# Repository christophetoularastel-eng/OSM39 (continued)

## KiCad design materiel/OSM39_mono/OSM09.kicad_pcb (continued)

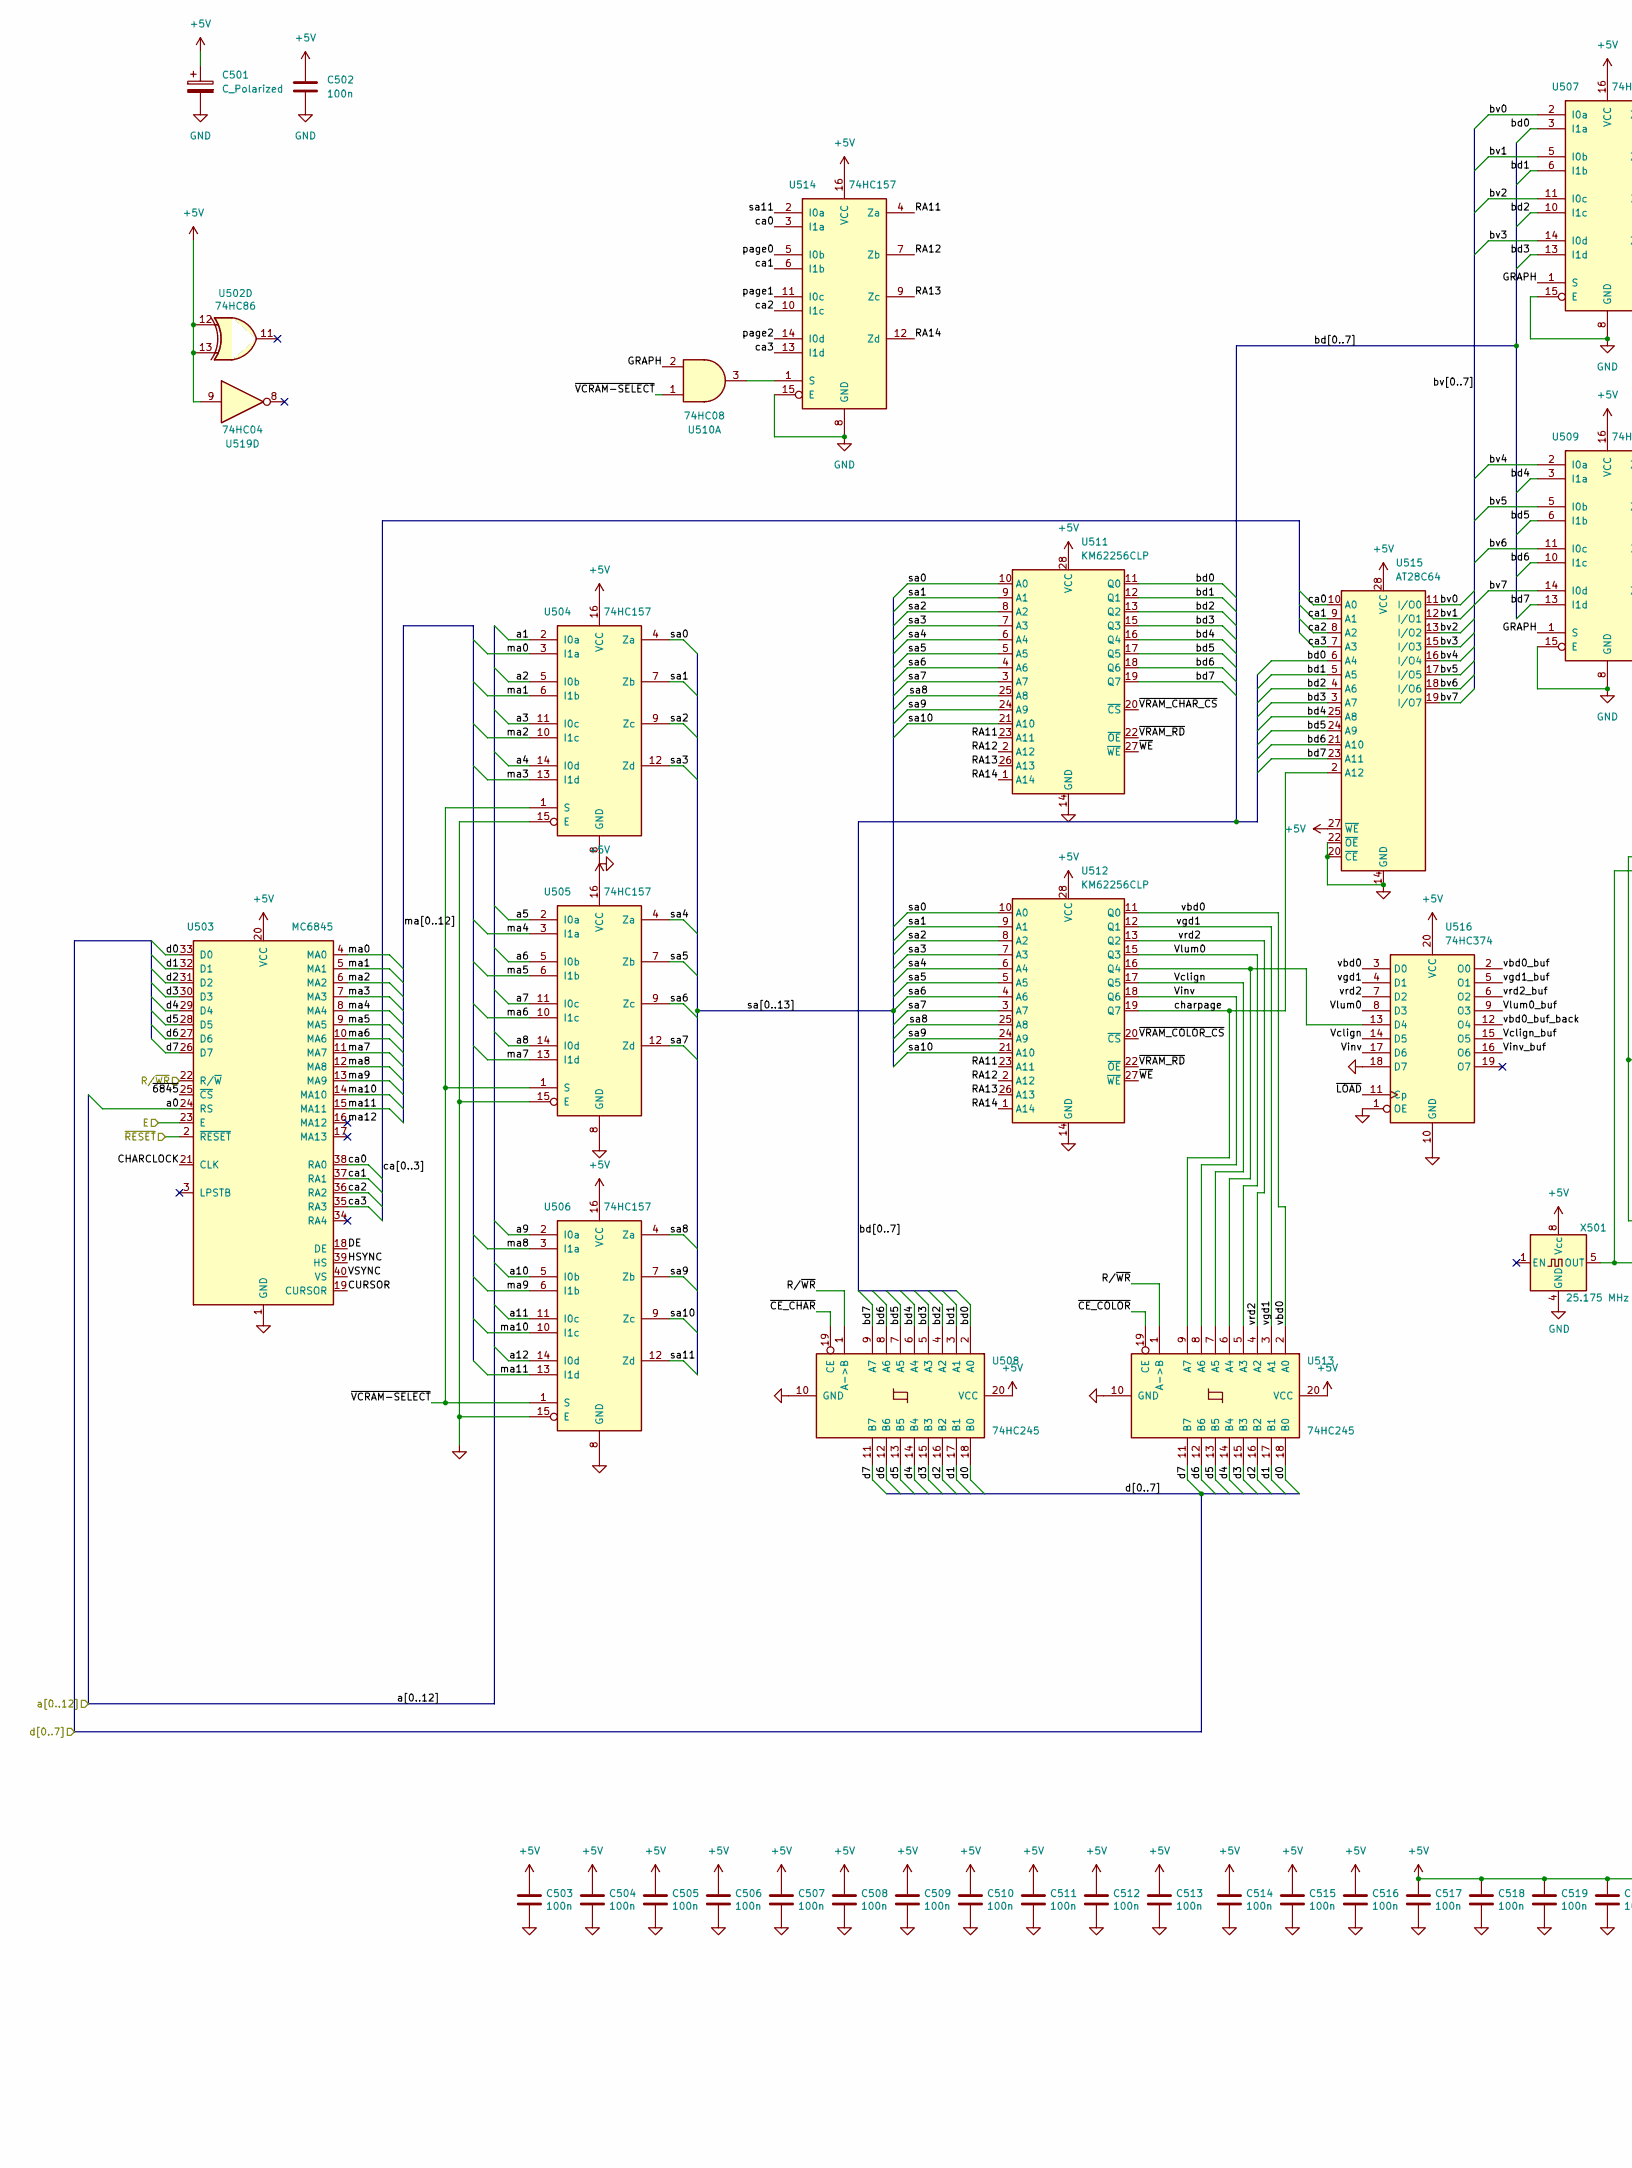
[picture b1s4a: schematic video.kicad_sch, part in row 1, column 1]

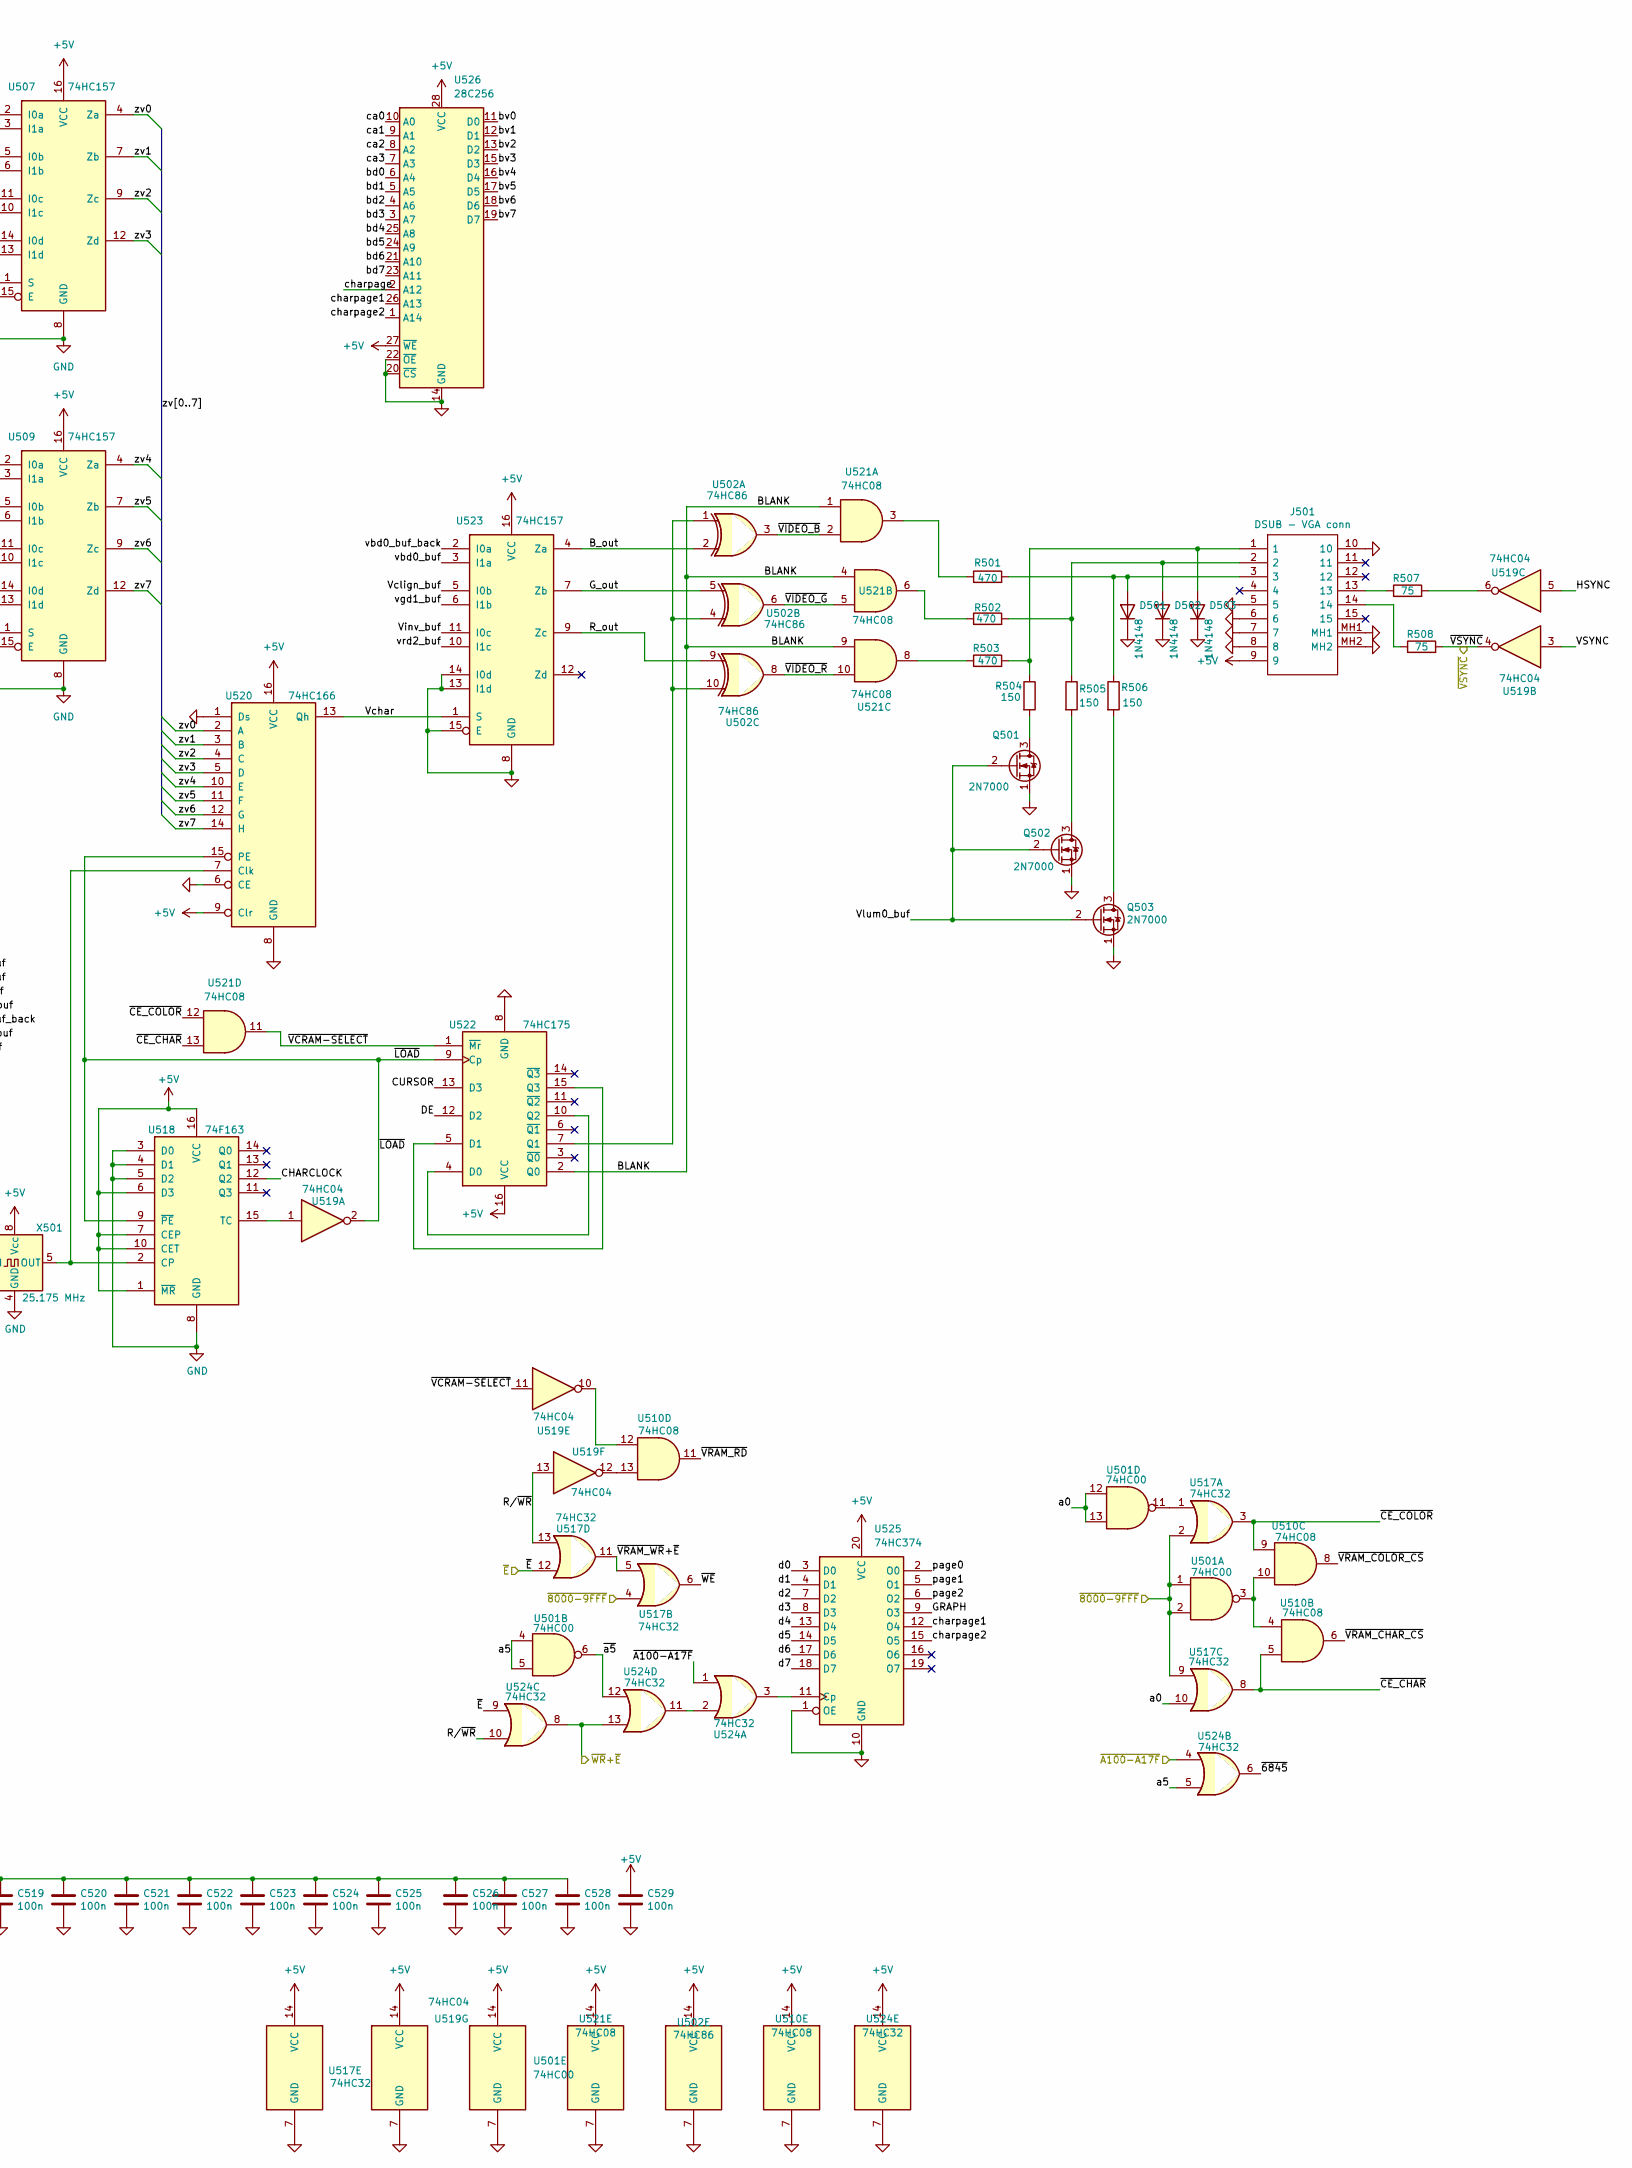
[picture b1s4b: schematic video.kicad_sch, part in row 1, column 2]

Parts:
C501: C_Polarized; CP_Radial_D4.0mm_P1.50mm
C502, C503, C504, C505, C506, C507, C508, C509, C510, C511, C512, C513, C514, C515, C516, C517, C518, C519, C520, C521, C522, C523, C524, C525, C526, C527, C528, C529: 100n; C_Disc_D5.0mm_W2.5mm_P2.50mm
D501, D502, D503: 1N4148; D_DO-35_SOD27_P7.62mm_Horizontal
J501: DSUB - VGA conn; D-Sub High Density Connectors; Mouser Part Number 571-2311586-4
Q501, Q502, Q503: 2N7000; TO-92_Inline
R501, R502, R503: 470; R_Axial_DIN0207_L6.3mm_D2.5mm_P10.16mm_Horizontal
R504, R505, R506: 150; R_Axial_DIN0207_L6.3mm_D2.5mm_P10.16mm_Horizontal
R507, R508: 75; R_Axial_DIN0207_L6.3mm_D2.5mm_P10.16mm_Horizontal
U501: 74HC00; DIP-14_W7.62mm_LongPads
U502: 74HC86; DIP-14_W7.62mm_LongPads
U503: MC6845; DIP-40_W15.24mm_LongPads
U504, U505, U506, U507, U509, U514, U523: 74HC157; DIP-16_W7.62mm_LongPads
U508, U513: 74HC245; DIP-20_W7.62mm_LongPads
U510, U521: 74HC08; DIP-14_W7.62mm_LongPads
U511, U512: KM62256CLP; DIP-28_W15.24mm_LongPads
U515: AT28C64; DIP-28_W15.24mm_LongPads
U516, U525: 74HC374; DIP-20_W7.62mm_LongPads
U517, U524: 74HC32; DIP-14_W7.62mm_LongPads
U518: 74F163; DIP-16_W7.62mm_LongPads
U519: 74HC04; DIP-14_W7.62mm_LongPads
U520: 74HC166; DIP-16_W7.62mm_LongPads
U522: 74HC175; DIP-16_W7.62mm_LongPads
U526: 28C256; DIP-28_W15.24mm_LongPads
X501: 25.175 MHz; Oscillator_DIP-8

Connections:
+5V: C501.1, C502.1, C503.1, C504.1, C505.1, C506.1, C507.1, C508.1, C509.1, C510.1, C511.1, C512.1, C513.1, C514.1, C515.1, C516.1, C517.1, C518.1, C519.1, C520.1, C521.1, C522.1, C523.1, C524.1, C525.1, C526.1, C527.1, C528.1, C529.1, J501.9, U501.14 (VCC), U502.12, U502.13, U502.14 (VCC), U503.20 (VCC), U504.16 (VCC), U505.16 (VCC), U506.16 (VCC), U507.16 (VCC), U508.20 (VCC), U509.16 (VCC), U510.14 (VCC), U511.28 (VCC), U512.28 (VCC), U513.20 (VCC), U514.16 (VCC), U515.27 (~WE), U515.28 (VCC), U516.20 (VCC), U517.14 (VCC), U518.1 (~MR), U518.6 (D3), U518.7 (CEP), U518.10 (CET), U518.16 (VCC), U519.9, U519.14 (VCC), U520.9 (Clr), U520.16 (VCC), U521.14 (VCC), U522.16 (VCC), U523.16 (VCC), U524.14 (VCC), U525.20 (VCC), U526.27 (~WE), U526.28 (VCC), X501.8 (Vcc); also elsewhere on the board
/8000-9FFF: U501.1, U501.2, U517.2, U517.4, U517.9; also elsewhere on the board
/A0: U501.12, U501.13, U503.24 (RS), U517.10; also elsewhere on the board
/A1: U504.2 (I0a); also elsewhere on the board
/A2: U504.5 (I0b); also elsewhere on the board
/A3: U504.11 (I0c); also elsewhere on the board
/A4: U504.14 (I0d); also elsewhere on the board
/A5: U501.4, U501.5, U505.2 (I0a), U524.5; also elsewhere on the board
/A6: U505.5 (I0b); also elsewhere on the board
/A7: U505.11 (I0c); also elsewhere on the board
/A8: U505.14 (I0d); also elsewhere on the board
/A9: U506.2 (I0a); also elsewhere on the board
/A10: U506.5 (I0b); also elsewhere on the board
/A11: U506.11 (I0c); also elsewhere on the board
/A12: U506.14 (I0d); also elsewhere on the board
/A100-A13F: U524.1, U524.4; also elsewhere on the board
/D0: U503.33 (D0), U508.18 (B0), U513.18 (B0), U525.3 (D0); also elsewhere on the board
/D1: U503.32 (D1), U508.17 (B1), U513.17 (B1), U525.4 (D1); also elsewhere on the board
/D2: U503.31 (D2), U508.16 (B2), U513.16 (B2), U525.7 (D2); also elsewhere on the board
/D3: U503.30 (D3), U508.15 (B3), U513.15 (B3), U525.8 (D3); also elsewhere on the board
/D4: U503.29 (D4), U508.14 (B4), U513.14 (B4), U525.13 (D4); also elsewhere on the board
/D5: U503.28 (D5), U508.13 (B5), U513.13 (B5), U525.14 (D5); also elsewhere on the board
/D6: U503.27 (D6), U508.12 (B6), U513.12 (B6), U525.17 (D6); also elsewhere on the board
/D7: U503.26 (D7), U508.11 (B7), U513.11 (B7), U525.18 (D7); also elsewhere on the board
/E: U503.23 (E); also elsewhere on the board
/R/~WR: U503.22 (R/~W), U508.1 (A->B), U513.1 (A->B), U517.13, U519.13, U524.10; also elsewhere on the board
/VSYNC: R508.2, U519.4; also elsewhere on the board
/video/BLANK: U521.1, U521.4, U521.9, U522.2 (Q0)
/video/B_out: U502.2, U523.4 (Za)
/video/CHARCLOCK: U503.21 (CLK), U518.12 (Q2)
/video/CURSOR: U503.19 (CURSOR), U522.13 (D3)
/video/DE: U503.18 (DE), U522.12 (D2)
/video/GRAPH: U507.1 (S), U509.1 (S), U510.2, U525.9 (O3)
/video/G_out: U502.5, U523.7 (Zb)
/video/HSYNC: U503.39 (HS), U519.5
/video/RA11: U511.23 (A11), U512.23 (A11), U514.4 (Za)
/video/RA12: U511.2 (A12), U512.2 (A12), U514.7 (Zb)
/video/RA13: U511.26 (A13), U512.26 (A13), U514.9 (Zc)
/video/RA14: U511.1 (A14), U512.1 (A14), U514.12 (Zd)
/video/R_out: U502.9, U523.9 (Zc)
/video/VSYNC: U503.40 (VS), U519.3
/video/Vchar: U520.13 (Qh), U523.1 (S)
/video/Vclign: U512.17 (Q5), U513.7 (A5), U516.14 (D5)
/video/Vclign_buf: U516.15 (O5), U523.5 (I0b)
/video/Vinv: U512.18 (Q6), U513.8 (A6), U516.17 (D6)
/video/Vinv_buf: U516.16 (O6), U523.11 (I0c)
/video/Vlum0: U512.15 (Q3), U513.5 (A3), U516.8 (D3)
/video/Vlum0_buf: Q501.2 (G), Q502.2 (G), Q503.2 (G), U516.9 (O3)
/video/bd0: U507.3 (I1a), U508.2 (A0), U511.11 (Q0), U515.6 (A4), U526.6 (A4)
/video/bd1: U507.6 (I1b), U508.3 (A1), U511.12 (Q1), U515.5 (A5), U526.5 (A5)
/video/bd2: U507.10 (I1c), U508.4 (A2), U511.13 (Q2), U515.4 (A6), U526.4 (A6)
/video/bd3: U507.13 (I1d), U508.5 (A3), U511.15 (Q3), U515.3 (A7), U526.3 (A7)
/video/bd4: U508.6 (A4), U509.3 (I1a), U511.16 (Q4), U515.25 (A8), U526.25 (A8)
/video/bd5: U508.7 (A5), U509.6 (I1b), U511.17 (Q5), U515.24 (A9), U526.24 (A9)
/video/bd6: U508.8 (A6), U509.10 (I1c), U511.18 (Q6), U515.21 (A10), U526.21 (A10)
/video/bd7: U508.9 (A7), U509.13 (I1d), U511.19 (Q7), U515.23 (A11), U526.23 (A11)
/video/bv0: U507.2 (I0a), U515.11 (I/O0), U526.11 (D0)
/video/bv1: U507.5 (I0b), U515.12 (I/O1), U526.12 (D1)
/video/bv2: U507.11 (I0c), U515.13 (I/O2), U526.13 (D2)
/video/bv3: U507.14 (I0d), U515.15 (I/O3), U526.15 (D3)
/video/bv4: U509.2 (I0a), U515.16 (I/O4), U526.16 (D4)
/video/bv5: U509.5 (I0b), U515.17 (I/O5), U526.17 (D5)
/video/bv6: U509.11 (I0c), U515.18 (I/O6), U526.18 (D6)
/video/bv7: U509.14 (I0d), U515.19 (I/O7), U526.19 (D7)
/video/ca0: U503.38 (RA0), U514.3 (I1a), U515.10 (A0), U526.10 (A0)
/video/ca1: U503.37 (RA1), U514.6 (I1b), U515.9 (A1), U526.9 (A1)
/video/ca2: U503.36 (RA2), U514.10 (I1c), U515.8 (A2), U526.8 (A2)
/video/ca3: U503.35 (RA3), U514.13 (I1d), U515.7 (A3), U526.7 (A3)
/video/charpage: U512.19 (Q7), U513.9 (A7), U515.2 (A12), U526.2 (A12)
/video/charpage1: U525.12 (O4), U526.26 (A13)
/video/charpage2: U525.15 (O5), U526.1 (A14)
/video/ma0: U503.4 (MA0), U504.3 (I1a)
/video/ma1: U503.5 (MA1), U504.6 (I1b)
/video/ma2: U503.6 (MA2), U504.10 (I1c)
/video/ma3: U503.7 (MA3), U504.13 (I1d)
/video/ma4: U503.8 (MA4), U505.3 (I1a)
/video/ma5: U503.9 (MA5), U505.6 (I1b)
/video/ma6: U503.10 (MA6), U505.10 (I1c)
/video/ma7: U503.11 (MA7), U505.13 (I1d)
/video/ma8: U503.12 (MA8), U506.3 (I1a)
/video/ma9: U503.13 (MA9), U506.6 (I1b)
/video/ma10: U503.14 (MA10), U506.10 (I1c)
/video/ma11: U503.15 (MA11), U506.13 (I1d)
/video/ma12: U503.16 (MA12)
/video/page0: U514.5 (I0b), U525.2 (O0)
/video/page1: U514.11 (I0c), U525.5 (O1)
/video/page2: U514.14 (I0d), U525.6 (O2)
/video/sa0: U504.4 (Za), U511.10 (A0), U512.10 (A0)
/video/sa1: U504.7 (Zb), U511.9 (A1), U512.9 (A1)
/video/sa2: U504.9 (Zc), U511.8 (A2), U512.8 (A2)
/video/sa3: U504.12 (Zd), U511.7 (A3), U512.7 (A3)
/video/sa4: U505.4 (Za), U511.6 (A4), U512.6 (A4)
/video/sa5: U505.7 (Zb), U511.5 (A5), U512.5 (A5)
/video/sa6: U505.9 (Zc), U511.4 (A6), U512.4 (A6)
/video/sa7: U505.12 (Zd), U511.3 (A7), U512.3 (A7)
/video/sa8: U506.4 (Za), U511.25 (A8), U512.25 (A8)
/video/sa9: U506.7 (Zb), U511.24 (A9), U512.24 (A9)
/video/sa10: U506.9 (Zc), U511.21 (A10), U512.21 (A10)
/video/sa11: U506.12 (Zd), U514.2 (I0a)
/video/vbd0: U512.11 (Q0), U513.2 (A0), U516.3 (D0)
/video/vbd0_buf: U516.2 (O0), U523.3 (I1a)
/video/vbd0_buf_back: U516.12 (O4), U523.2 (I0a)
/video/vgd1: U512.12 (Q1), U513.3 (A1), U516.4 (D1)
/video/vgd1_buf: U516.5 (O1), U523.6 (I1b)
/video/vrd2: U512.13 (Q2), U513.4 (A2), U516.7 (D2)
/video/vrd2_buf: U516.6 (O2), U523.10 (I1c)
/video/zv0: U507.4 (Za), U520.2 (A)
/video/zv1: U507.7 (Zb), U520.3 (B)
/video/zv2: U507.9 (Zc), U520.4 (C)
/video/zv3: U507.12 (Zd), U520.5 (D)
/video/zv4: U509.4 (Za), U520.10 (E)
/video/zv5: U509.7 (Zb), U520.11 (F)
/video/zv6: U509.9 (Zc), U520.12 (G)
/video/zv7: U509.12 (Zd), U520.14 (H)
/video/~6845: U503.25 (~CS), U524.6
/video/~CE_CHAR: U508.19 (CE), U510.5, U517.8, U521.13
/video/~CE_COLOR: U510.9, U513.19 (CE), U517.3, U521.12
/video/~LOAD: U516.11 (Cp), U518.9 (~PE), U519.2, U520.15 (PE), U522.9 (Cp)
/video/~VCRAM-SELECT: U504.1 (S), U505.1 (S), U506.1 (S), U510.1, U519.11, U521.11, U522.1 (~Mr)
/video/~VIDEO_B: U502.3, U521.2
/video/~VIDEO_G: U502.6, U521.5
/video/~VIDEO_R: U502.8, U521.10
/video/~VRAM_CHAR_CS: U510.6, U511.20 (~CS)
/video/~VRAM_COLOR_CS: U510.8, U512.20 (~CS)
/video/~VRAM_RD: U510.11, U511.22 (~OE), U512.22 (~OE)
/video/~VRAM_WR+~E: U517.5, U517.11
/video/~WE: U511.27 (~WE), U512.27 (~WE), U517.6
/video/~a5: U501.6, U524.12
/~E: U517.12, U524.9; also elsewhere on the board
/~RESET: U503.2 (~RESET); also elsewhere on the board
/~WR+~E: U524.8, U524.13; also elsewhere on the board
GND: C501.2, C502.2, C503.2, C504.2, C505.2, C506.2, C507.2, C508.2, C509.2, C510.2, C511.2, C512.2, C513.2, C514.2, C515.2, C516.2, C517.2, C518.2, C519.2, C520.2, C521.2, C522.2, C523.2, C524.2, C525.2, C526.2, C527.2, C528.2, C529.2, D501.1 (K), D502.1 (K), D503.1 (K), J501.5, J501.6, J501.7, J501.8, J501.10, J501.MH1, J501.MH2, Q501.1 (S), Q502.1 (S), Q503.1 (S), U501.7 (GND), U502.7 (GND), U503.1 (GND), U504.8 (GND), U504.15 (E), U505.8 (GND), U505.15 (E), U506.8 (GND), U506.15 (E), U507.8 (GND), U507.15 (E), U508.10 (GND), U509.8 (GND), U509.15 (E), U510.7 (GND), U511.14 (GND), U512.14 (GND), U513.10 (GND), U514.8 (GND), U514.15 (E), U515.14 (GND), U515.20 (~CE), U515.22 (~OE), U516.1 (OE), U516.10 (GND), U516.18 (D7), U517.7 (GND), U518.3 (D0), U518.4 (D1), U518.5 (D2), U518.8 (GND), U519.7 (GND), U520.1 (Ds), U520.6 (CE), U520.8 (GND), U521.7 (GND), U522.8 (GND), U523.8 (GND), U523.13 (I1d), U523.14 (I0d), U523.15 (E), U524.7 (GND), U525.1 (OE), U525.10 (GND), U526.14 (GND), U526.20 (~CS), U526.22 (~OE), X501.4 (GND); also elsewhere on the board
unnamed: D501.2 (A), J501.3, R501.2, R506.1
unnamed: D502.2 (A), J501.2, R502.2, R505.1
unnamed: D503.2 (A), J501.1, R503.2, R504.1
unnamed: J501.13, R507.1
unnamed: J501.14, R508.1
unnamed: Q501.3 (D), R504.2
unnamed: Q502.3 (D), R505.2
unnamed: Q503.3 (D), R506.2
unnamed: R501.1, U521.3
unnamed: R502.1, U521.6
unnamed: R503.1, U521.8
unnamed: R507.2, U519.6
unnamed: U501.3, U510.4, U510.10
unnamed: U501.11, U517.1
unnamed: U510.12, U519.10
unnamed: U510.13, U519.12
unnamed: U512.16 (Q4), U513.6 (A4), U516.13 (D4)
unnamed: U510.3, U514.1 (S)
unnamed: U518.2 (CP), U520.7 (Clk), X501.5 (OUT)
unnamed: U518.15 (TC), U519.1
unnamed: U522.4 (D0), U522.10 (Q2)
unnamed: U522.5 (D1), U522.15 (Q3)
unnamed: U502.1, U502.4, U502.10, U522.7 (Q1)
unnamed: U524.2, U524.11
unnamed: U524.3, U525.11 (Cp)

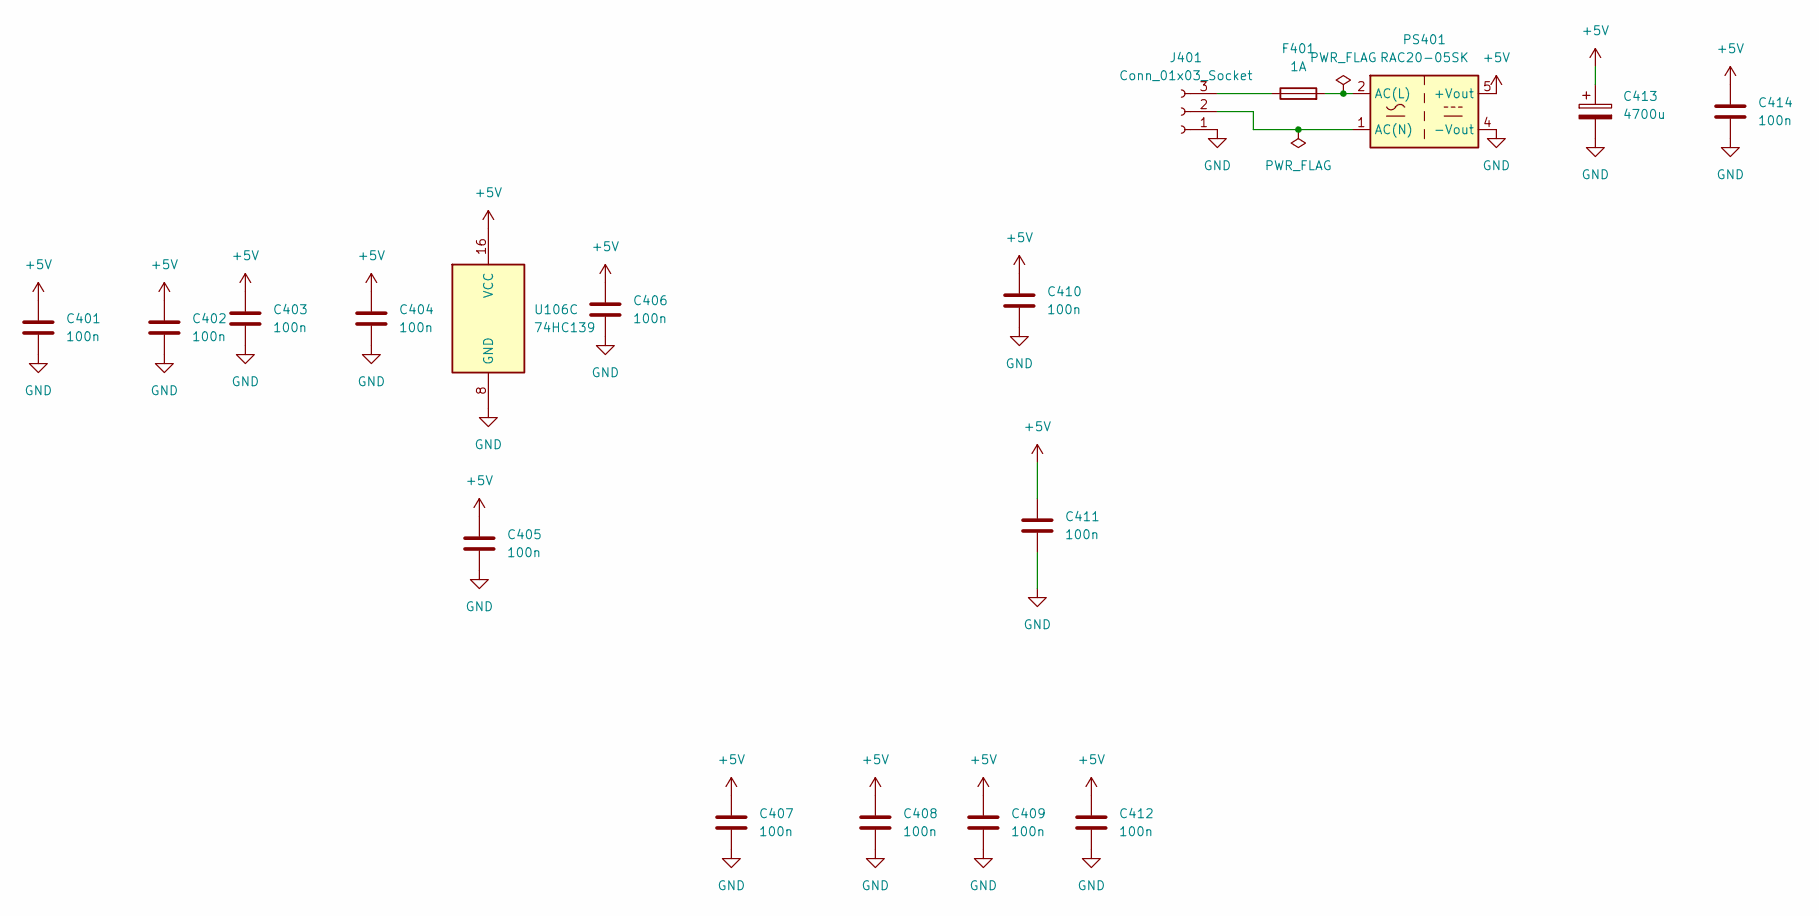
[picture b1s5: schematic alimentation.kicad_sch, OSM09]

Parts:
C401, C402, C403, C404, C405, C406, C407, C408, C409, C410, C411, C412, C414: 100n; C_Disc_D5.0mm_W2.5mm_P2.50mm
C413: 4700u; CP_Radial_Tantal_D10.5mm_P5.00mm
F401: 1A; Fuseholder_TR5_Littelfuse_No560_No460
J401: Conn_01x03_Socket; PhoenixContact_MSTBVA_2,5_3-G-5,08_1x03_P5.08mm_Vertical
PS401: RAC20-05SK; Converter_ACDC_Recom_RAC20-xxSK_THT
U106: 74HC139; DIP-16_W7.62mm_LongPads

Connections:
+5V: C401.1, C402.1, C403.1, C404.1, C405.1, C406.1, C407.1, C408.1, C409.1, C410.1, C411.1, C412.1, C413.1, C414.1, PS401.5 (+Vout), U106.16 (VCC); also elsewhere on the board
GND: C401.2, C402.2, C403.2, C404.2, C405.2, C406.2, C407.2, C408.2, C409.2, C410.2, C411.2, C412.2, C413.2, C414.2, J401.1, PS401.4 (-Vout), U106.8 (GND); also elsewhere on the board
unnamed: J401.2, PS401.1 (AC(N))
unnamed: F401.1, J401.3
unnamed: F401.2, PS401.2 (AC(L))

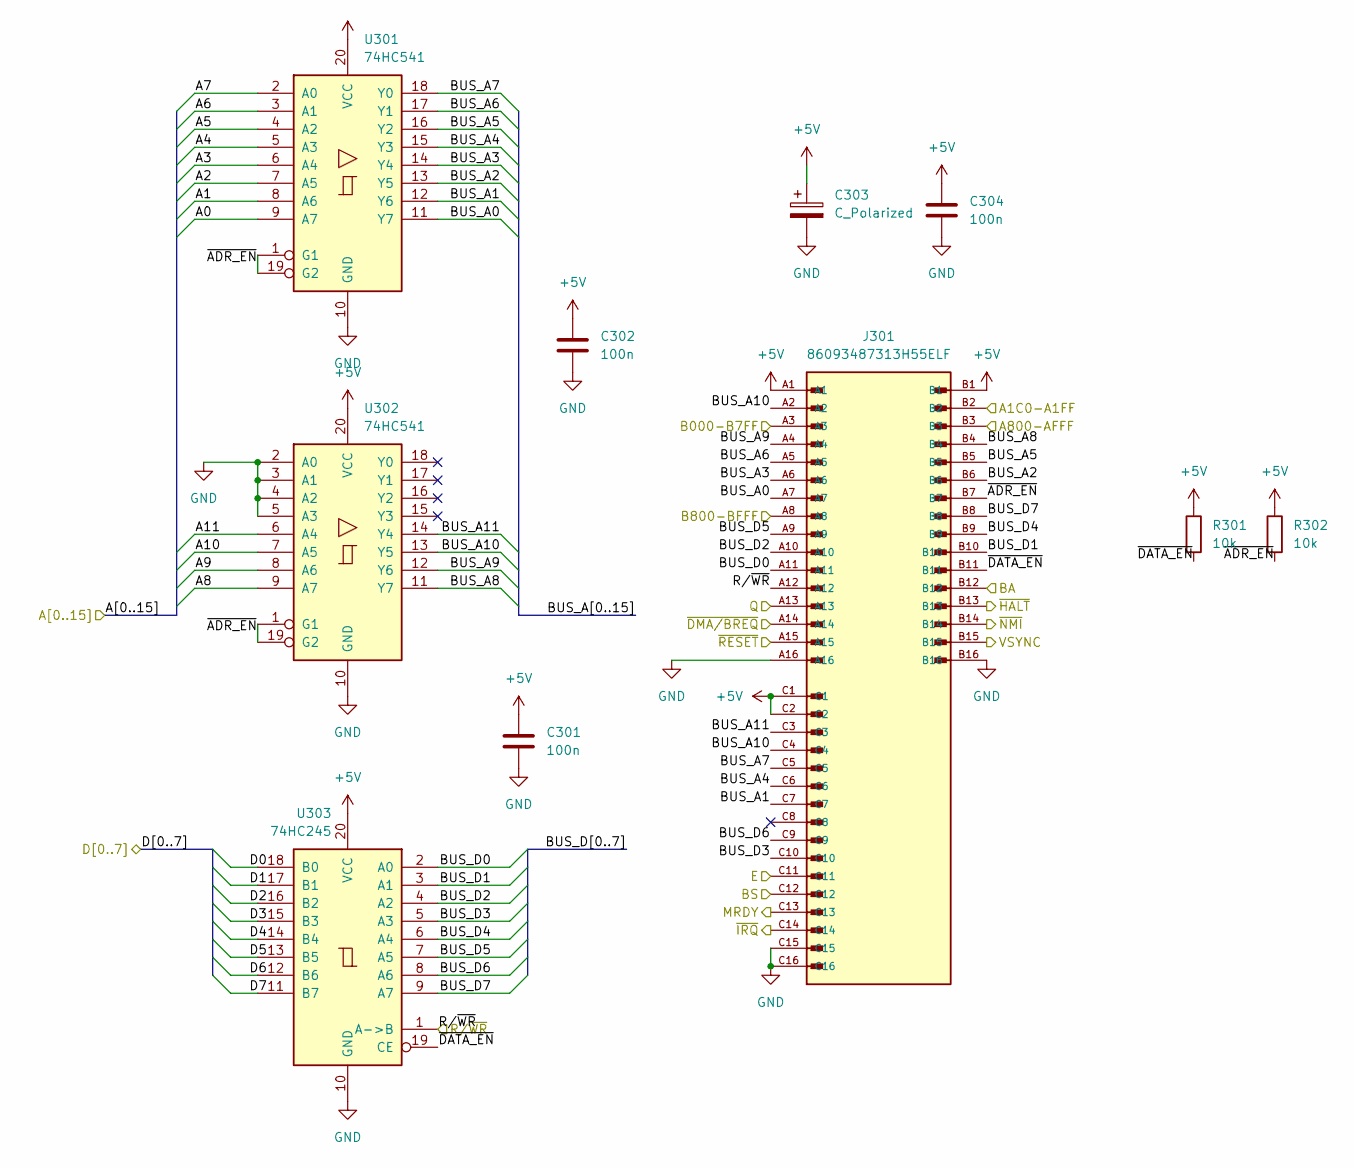
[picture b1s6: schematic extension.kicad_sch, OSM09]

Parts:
C301, C302, C304: 100n; C_Disc_D5.0mm_W2.5mm_P2.50mm
C303: C_Polarized; CP_Radial_D4.0mm_P1.50mm
J301: 86093487313H55ELF; AMPHENOL_86093487313H55ELF; PARTREV H
R301, R302: 10k; R_Axial_DIN0204_L3.6mm_D1.6mm_P7.62mm_Horizontal
U301, U302: 74HC541; DIP-20_W7.62mm_LongPads
U303: 74HC245; DIP-20_W7.62mm_LongPads

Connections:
+5V: C301.1, C302.1, C303.1, C304.1, J301.A1, J301.B1, J301.C1, J301.C2, R301.1, R302.1, U301.20 (VCC), U302.20 (VCC), U303.20 (VCC); also elsewhere on the board
/A0: U301.9 (A7); also elsewhere on the board
/A1: U301.8 (A6); also elsewhere on the board
/A1C0-A1FF: J301.B2; also elsewhere on the board
/A2: U301.7 (A5); also elsewhere on the board
/A3: U301.6 (A4); also elsewhere on the board
/A4: U301.5 (A3); also elsewhere on the board
/A5: U301.4 (A2); also elsewhere on the board
/A6: U301.3 (A1); also elsewhere on the board
/A7: U301.2 (A0); also elsewhere on the board
/A8: U302.9 (A7); also elsewhere on the board
/A9: U302.8 (A6); also elsewhere on the board
/A10: U302.7 (A5); also elsewhere on the board
/A11: U302.6 (A4); also elsewhere on the board
/A800-AFFF: J301.B3; also elsewhere on the board
/B000-B7FF: J301.A3; also elsewhere on the board
/B800-BFFF: J301.A8; also elsewhere on the board
/BA: J301.B12; also elsewhere on the board
/BS: J301.C12; also elsewhere on the board
/D0: U303.18 (B0); also elsewhere on the board
/D1: U303.17 (B1); also elsewhere on the board
/D2: U303.16 (B2); also elsewhere on the board
/D3: U303.15 (B3); also elsewhere on the board
/D4: U303.14 (B4); also elsewhere on the board
/D5: U303.13 (B5); also elsewhere on the board
/D6: U303.12 (B6); also elsewhere on the board
/D7: U303.11 (B7); also elsewhere on the board
/E: J301.C11; also elsewhere on the board
/MRDY: J301.C13; also elsewhere on the board
/Q: J301.A13; also elsewhere on the board
/R/~WR: J301.A12, U303.1 (A->B); also elsewhere on the board
/VSYNC: J301.B15; also elsewhere on the board
/extension/BUS_A0: J301.A7, U301.11 (Y7)
/extension/BUS_A1: J301.C7, U301.12 (Y6)
/extension/BUS_A2: J301.B6, U301.13 (Y5)
/extension/BUS_A3: J301.A6, U301.14 (Y4)
/extension/BUS_A4: J301.C6, U301.15 (Y3)
/extension/BUS_A5: J301.B5, U301.16 (Y2)
/extension/BUS_A6: J301.A5, U301.17 (Y1)
/extension/BUS_A7: J301.C5, U301.18 (Y0)
/extension/BUS_A8: J301.B4, U302.11 (Y7)
/extension/BUS_A9: J301.A4, U302.12 (Y6)
/extension/BUS_A10: J301.A2, J301.C4, U302.13 (Y5)
/extension/BUS_A11: J301.C3, U302.14 (Y4)
/extension/BUS_D0: J301.A11, U303.2 (A0)
/extension/BUS_D1: J301.B10, U303.3 (A1)
/extension/BUS_D2: J301.A10, U303.4 (A2)
/extension/BUS_D3: J301.C10, U303.5 (A3)
/extension/BUS_D4: J301.B9, U303.6 (A4)
/extension/BUS_D5: J301.A9, U303.7 (A5)
/extension/BUS_D6: J301.C9, U303.8 (A6)
/extension/BUS_D7: J301.B8, U303.9 (A7)
/extension/~ADR_EN: J301.B7, R302.2, U301.1 (G1), U301.19 (G2), U302.1 (G1), U302.19 (G2)
/extension/~DATA_EN: J301.B11, R301.2, U303.19 (CE)
/~DMA/BREQ: J301.A14; also elsewhere on the board
/~HALT: J301.B13; also elsewhere on the board
/~IRQ: J301.C14; also elsewhere on the board
/~NMI: J301.B14; also elsewhere on the board
/~RESET: J301.A15; also elsewhere on the board
GND: C301.2, C302.2, C303.2, C304.2, J301.A16, J301.B16, J301.C15, J301.C16, U301.10 (GND), U302.2 (A0), U302.3 (A1), U302.4 (A2), U302.5 (A3), U302.10 (GND), U303.10 (GND); also elsewhere on the board

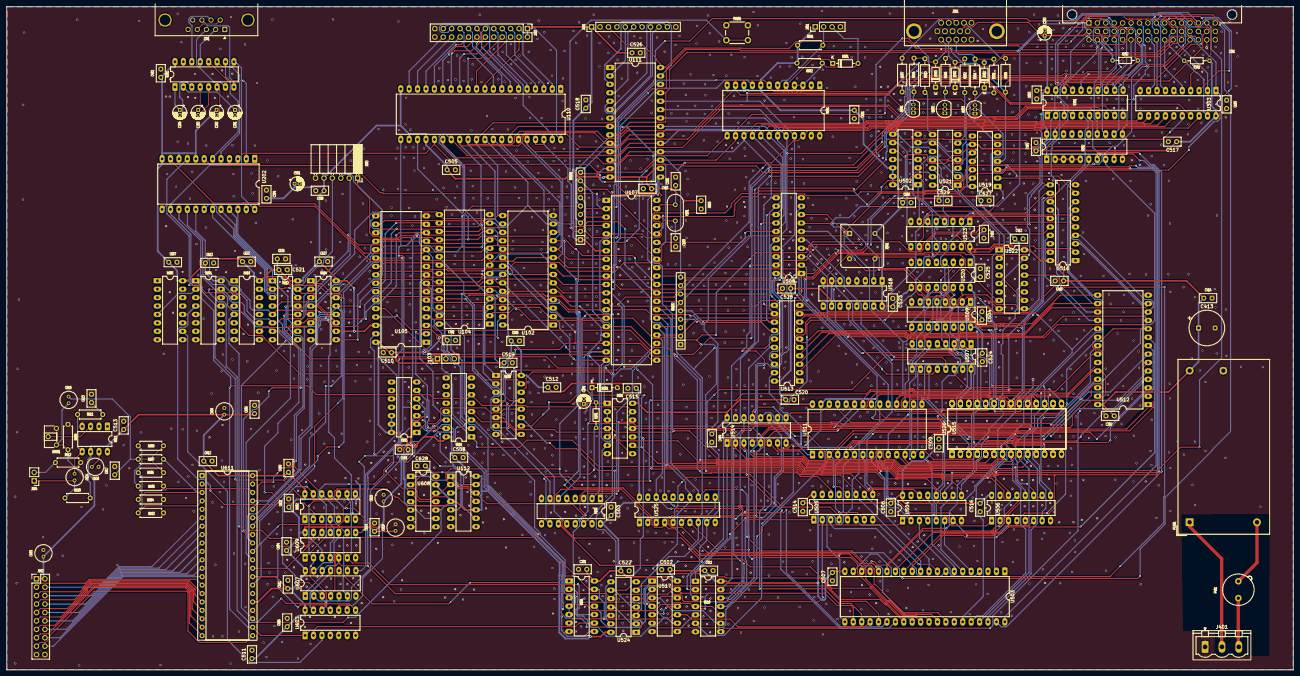
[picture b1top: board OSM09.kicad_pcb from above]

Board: 2 copper layers, 388.1 x 200.0 mm, 188 parts (0 on the bottom side), 319 nets.
